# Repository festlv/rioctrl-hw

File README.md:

# rioctrl- a modular hardware for riocore

rioctrl is modular open source CNC controller hardware for [riocore](https://github.com/multigcs/riocore/).

It consists of a main FPGA controller board which has 6 slots for various input/output modules.

At this time, the following modules have been designed:

* [rioctrl-controller](rioctrl-controller/README.md): Lattice ECP5 based controller board
* [rioctrl-stepdir4](rioctrl-stepdir4/README.md): 4 axis step/dir output interface
* [rioctrl-quadenc4](rioctrl-quadenc4/README.md): 4 axis quadrature encoder (ABZ) input
* [rioctrl-shifio](rioctrl-shiftio/README.md): 16 digital inputs, 16 digital outputs (PNP)
* breakouts/lichuan-lc10: breakout board that allows connecting Lichuan LC10 series servo to stepdir4 and quadenc4 module (via off-the-shelf RJ45 cables)
* breakouts/rj45-screw-terminals: breakout board from RJ45 cable to screw terminals
* breakouts/ditron-dc11-encoder: breakout board from RJ45 cable to Ditron DC11 glass scale optical encoder (DB9)

# Current state of the hardware design

The following hardware has been built and tested to be working:

* rioctrl-controller v1.0: minor rework was needed (remove a diode, rotate Y1 by 90 degrees). Fixed in v1.1.
* rioctrl-stepdir4 v1.0: electrically working, mechanically a connector was offset by 4 mm, fixed in v1.1.
* rioctrl-shiftio: working as designed.
* rioctrl-quadencz: working as designed (with the caveat that it's only compatible with differential/RS422 encoders).
* breakouts/ditron-dc11-encoder: working as designed, tested with Ditron DC11 encoder with RS422 output option.
* breakouts/rj45-screw-terminals: working as designed.
* breakouts/lichuan-lc10: step/dir/enable working as designed, GPIOs not tested yet.

## Known issues

* External override for slot enable is slow to turn off stepdir enable signals. Need to scope this a bit, but it's either due to U14 output being
  tri-stated or the capacitance of +24V_EN lines powering the enable signals for some additional time.
# Pretty images

### rioctrl-controller

### rioctrl-stepdir4

### rioctrl-quadenc4

### rioctrl-shiftio

### breakouts/lichuan-lc10

### breakouts/rj45-screw-terminals

## build.py

There is a `build.py` script that publishes outputs to each module `outputs` directory. It uses `<module>/version` file to
determine the current version, which should be updated accordingly.

For 3D renders of the boards, kicad-nightly package is needed, as the currently stable kicad version does not have board rendering functionality available from command line.

# License

The hardware designs in this repository are licensed under [CERN Open Hardware Licence Version 2 - Strongly Reciprocal](LICENSE.md).

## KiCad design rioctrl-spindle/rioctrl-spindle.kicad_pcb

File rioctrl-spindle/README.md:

# rioctrl-spindle

This module provides:
* 2 analog outputs (0..10V)
* RS-485 interface for Modbus
* RS-422 interface (for full-duplex serial communication, pending software support)
* Differential encoder interface

__Only analog outputs and Modbus has been tested!__

## Pinout

|       |          |
|-------|----------|
| AIN0  | GND      |
| AIN1  | SER_TX_A |
| MODBUS_A | SER_TX_B |
| MODBUS_B | SER_RX_A |
| x     | SER_RX_B |

# Changelog

## v1.0
Initial released version.

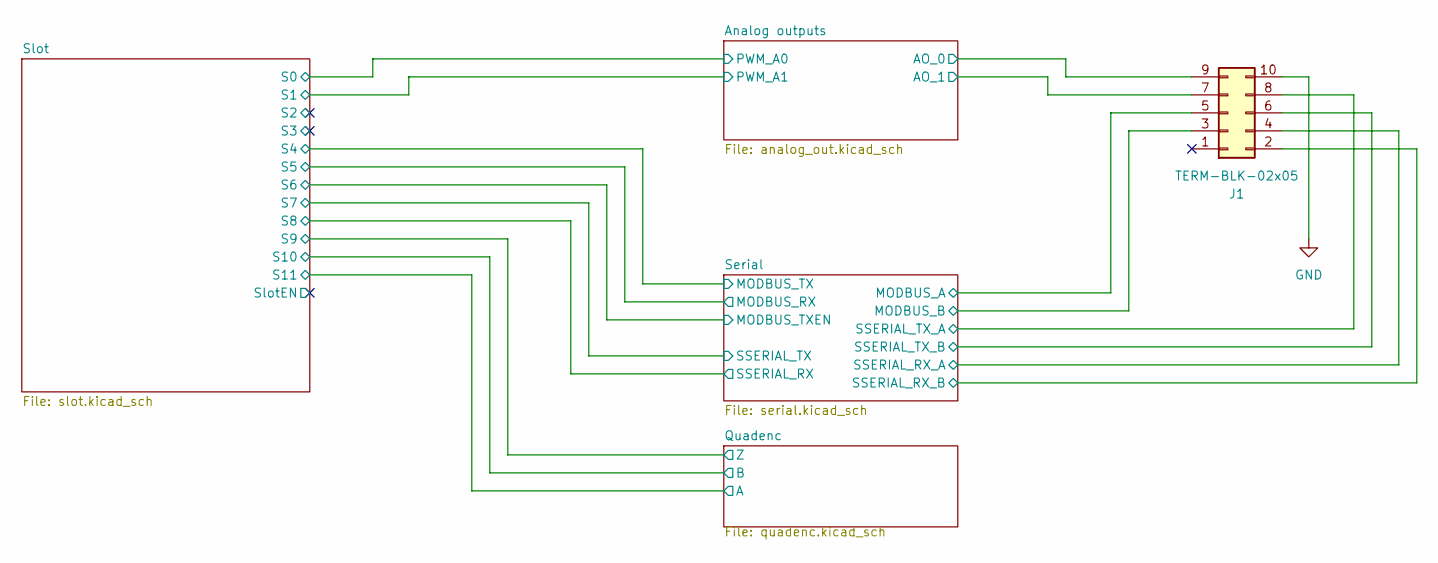
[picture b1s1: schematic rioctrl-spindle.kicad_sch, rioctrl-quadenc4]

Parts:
J1: TERM-BLK-02x05; JL15EDGRHC-35005B02; MPN JL15EDGRHC-35005B02; LCSC# C2908411

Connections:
/Analog outputs/AO_0: J1.9; also elsewhere on the board
/Analog outputs/AO_1: J1.7; also elsewhere on the board
/Serial/MODBUS_A: J1.5; also elsewhere on the board
/Serial/MODBUS_B: J1.3; also elsewhere on the board
/Serial/SSERIAL_RX_A: J1.4; also elsewhere on the board
/Serial/SSERIAL_RX_B: J1.2; also elsewhere on the board
/Serial/SSERIAL_TX_A: J1.8; also elsewhere on the board
/Serial/SSERIAL_TX_B: J1.6; also elsewhere on the board
GND: J1.10; also elsewhere on the board

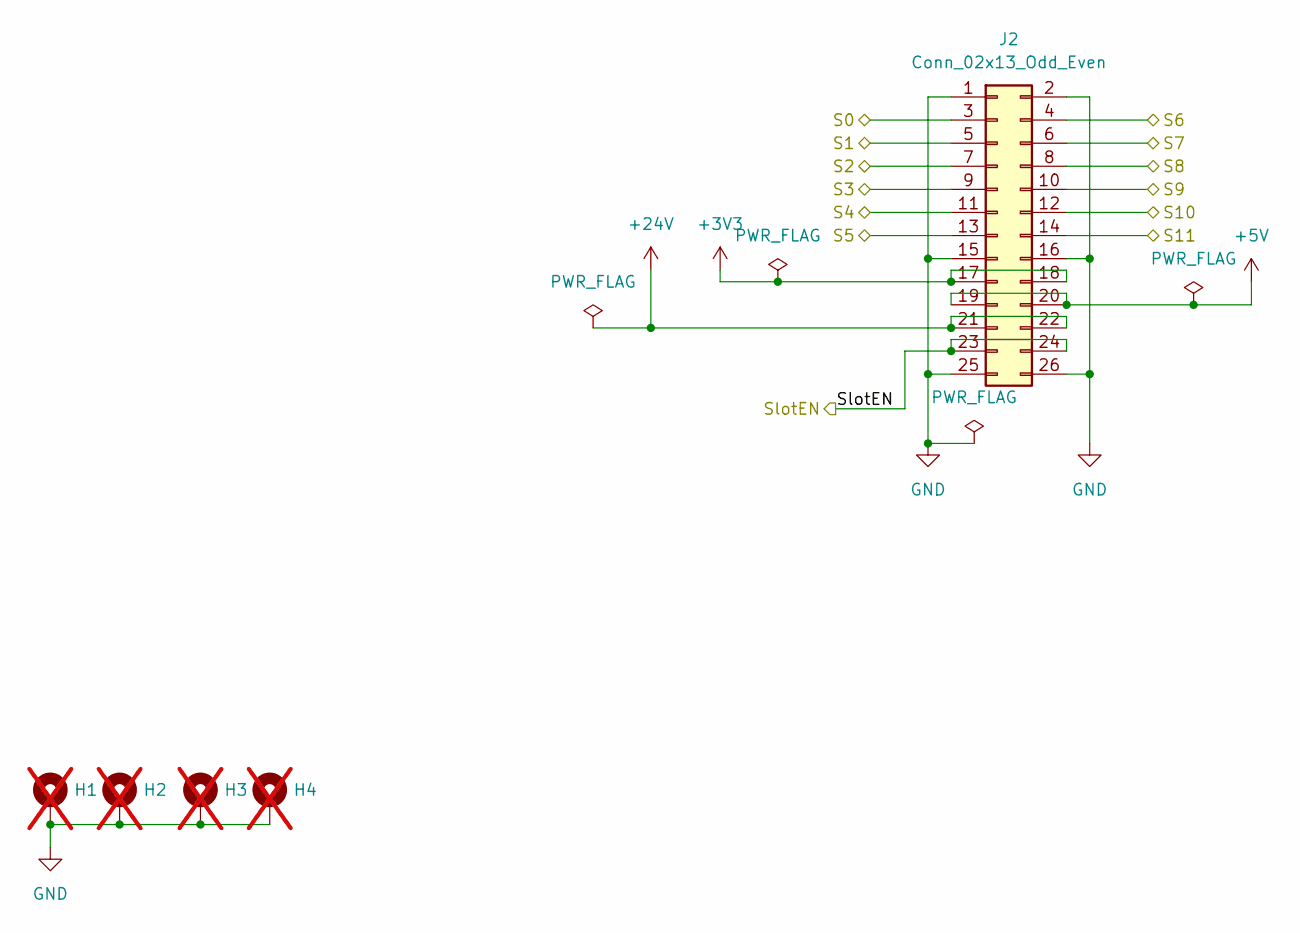
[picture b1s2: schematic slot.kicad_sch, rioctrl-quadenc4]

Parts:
H1, H2, H3, H4: MH_3.2mm; MountingHole_3.2mm_M3_Pad_Via; not fitted
J2: Conn_02x13_Odd_Even; PinHeader_2x13_P2.54mm_Horizontal; LCSC# C2894993

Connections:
+3V3: J2.17, J2.18; also elsewhere on the board
+5V: J2.19, J2.20; also elsewhere on the board
+24V: J2.21, J2.22; also elsewhere on the board
/Analog outputs/PWM_A0: J2.3; also elsewhere on the board
/Analog outputs/PWM_A1: J2.5; also elsewhere on the board
/Quadenc/A: J2.14; also elsewhere on the board
/Quadenc/B: J2.12; also elsewhere on the board
/Quadenc/Z: J2.10; also elsewhere on the board
/Serial/MODBUS_RX: J2.13; also elsewhere on the board
/Serial/MODBUS_TX: J2.11; also elsewhere on the board
/Serial/MODBUS_TXEN: J2.4; also elsewhere on the board
/Serial/SSERIAL_RX: J2.8; also elsewhere on the board
/Serial/SSERIAL_TX: J2.6; also elsewhere on the board
/Slot/S2: J2.7
/Slot/S3: J2.9
/Slot/SlotEN: J2.23, J2.24
GND: H1.1, H2.1, H3.1, H4.1, J2.1, J2.2, J2.15, J2.16, J2.25, J2.26; also elsewhere on the board

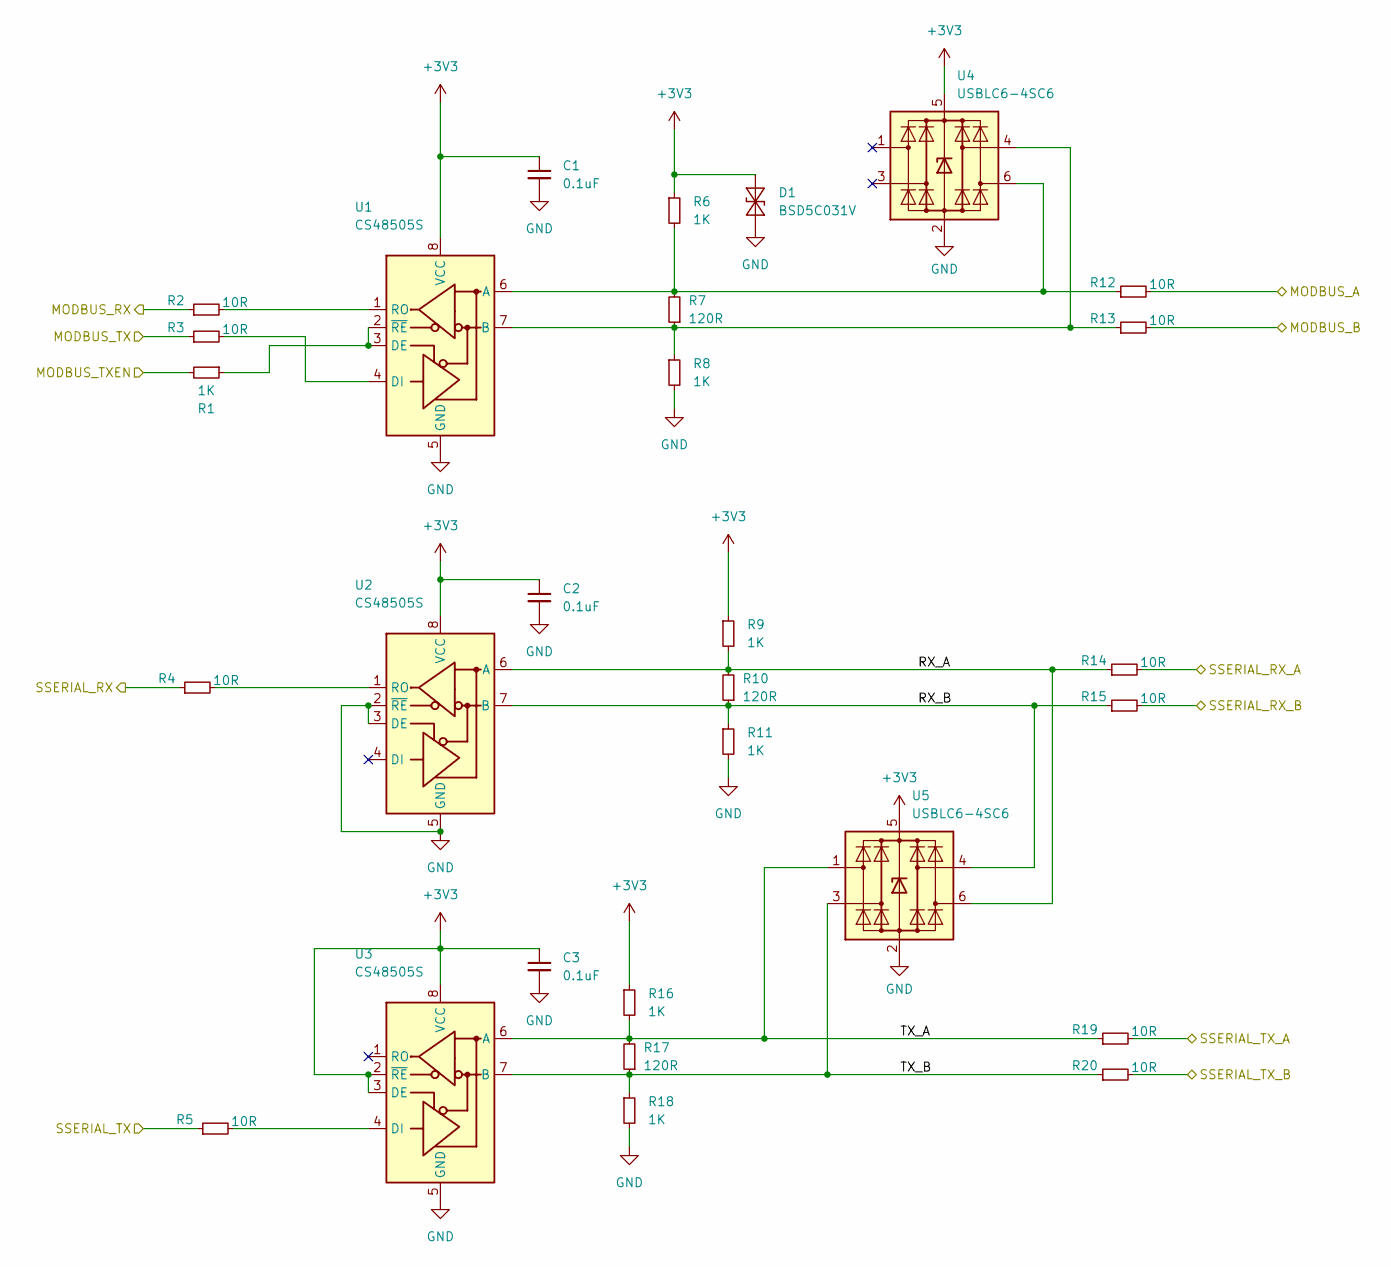
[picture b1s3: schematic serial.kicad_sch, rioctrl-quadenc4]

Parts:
C1, C2, C3: 0.1uF; C_0603_1608Metric; LCSC# C14663
D1: BSD5C031V; D_SOD-523; MPN BSD5C031V; LCSC# C151984
R1, R6, R8, R9, R11, R16, R18: 1K; R_0603_1608Metric; LCSC# C22548
R2, R3, R4, R5, R12, R13, R14, R15, R19, R20: 10R; R_0603_1608Metric; LCSC# C109318
R7, R10, R17: 120R; R_0603_1608Metric; LCSC# C114640
U1, U2, U3: CS48505S; SOIC-8_3.9x4.9mm_P1.27mm; MPN CS48505S; LCSC# C3202824
U4, U5: USBLC6-4SC6; SOT-23-6; MPN USBLC6-4SC6; LCSC# C5197386

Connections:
+3V3: C1.1, C2.1, C3.1, D1.1 (A1), R6.1, R9.1, R16.1, U1.8 (VCC), U2.8 (VCC), U3.2 (~RE), U3.3 (DE), U3.8 (VCC), U4.5 (VBUS), U5.5 (VBUS); also elsewhere on the board
/Serial/MODBUS_A: R12.2; also elsewhere on the board
/Serial/MODBUS_B: R13.2; also elsewhere on the board
/Serial/MODBUS_RX: R2.1; also elsewhere on the board
/Serial/MODBUS_TX: R3.1; also elsewhere on the board
/Serial/MODBUS_TXEN: R1.2; also elsewhere on the board
/Serial/RX_A: R9.2, R10.2, R14.1, U2.6 (A), U5.6 (I/O4)
/Serial/RX_B: R10.1, R11.1, R15.1, U2.7 (B), U5.4 (I/O3)
/Serial/SSERIAL_RX: R4.1; also elsewhere on the board
/Serial/SSERIAL_RX_A: R14.2; also elsewhere on the board
/Serial/SSERIAL_RX_B: R15.2; also elsewhere on the board
/Serial/SSERIAL_TX: R5.1; also elsewhere on the board
/Serial/SSERIAL_TX_A: R19.2; also elsewhere on the board
/Serial/SSERIAL_TX_B: R20.2; also elsewhere on the board
/Serial/TX_A: R16.2, R17.2, R19.1, U3.6 (A), U5.1 (I/O1)
/Serial/TX_B: R17.1, R18.1, R20.1, U3.7 (B), U5.3 (I/O2)
GND: C1.2, C2.2, C3.2, D1.2 (A2), R8.2, R11.2, R18.2, U1.5 (GND), U2.2 (~RE), U2.3 (DE), U2.5 (GND), U3.5 (GND), U4.2 (GND), U5.2 (GND); also elsewhere on the board
unnamed: R6.2, R7.2, R12.1, U1.6 (A), U4.6 (I/O4)
unnamed: R7.1, R8.1, R13.1, U1.7 (B), U4.4 (I/O3)
unnamed: R1.1, U1.2 (~RE), U1.3 (DE)
unnamed: R3.2, U1.4 (DI)
unnamed: R2.2, U1.1 (RO)
unnamed: R4.2, U2.1 (RO)
unnamed: R5.2, U3.4 (DI)

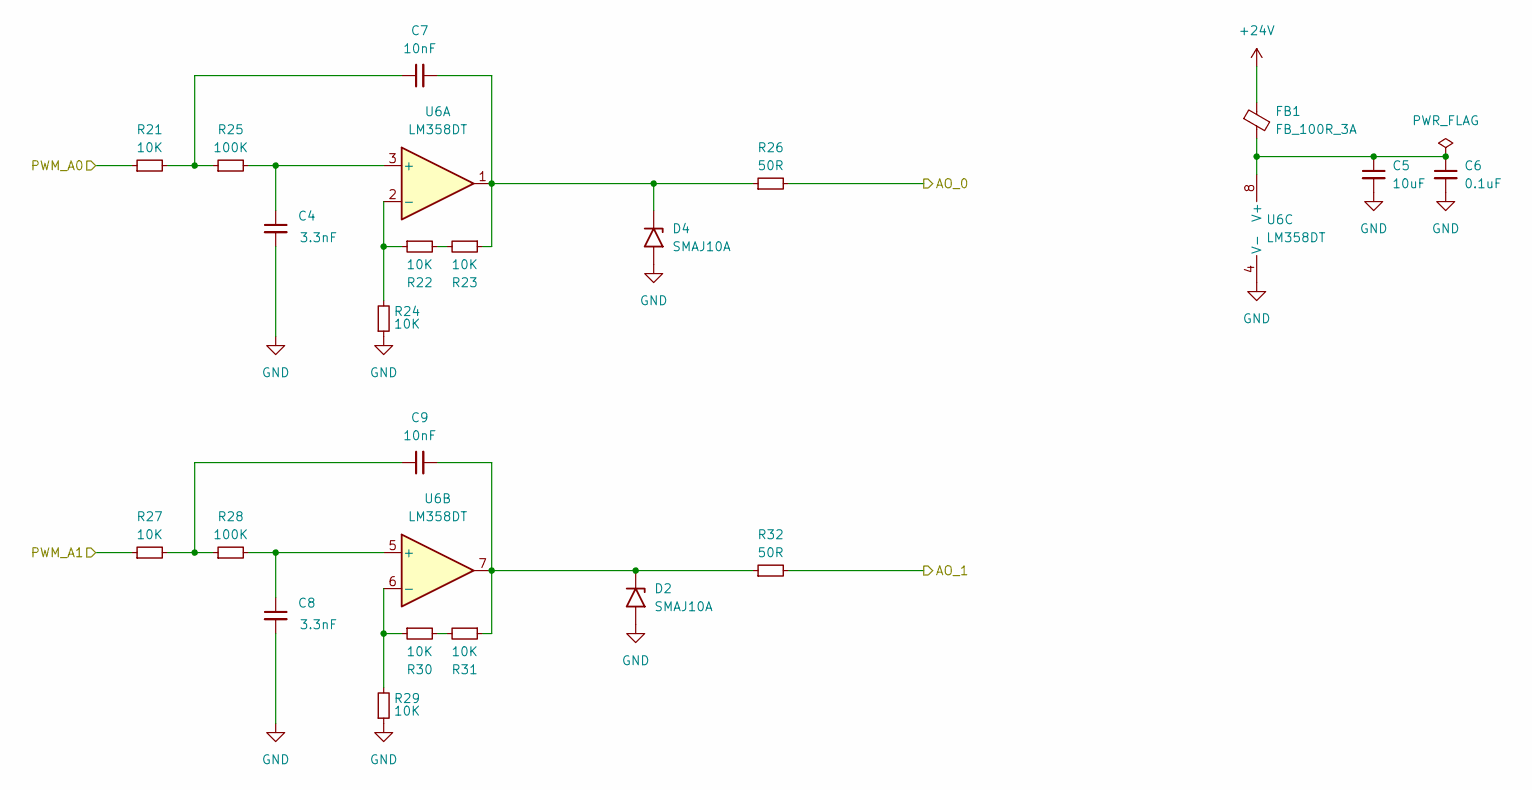
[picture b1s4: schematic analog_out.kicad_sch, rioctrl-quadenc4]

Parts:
C4, C8: 3.3nF; C_0603_1608Metric
C5: 10uF; C_0603_1608Metric
C6: 0.1uF; C_0603_1608Metric
C7, C9: 10nF; C_0603_1608Metric
D2, D4: SMAJ10A; D_SMA
FB1: FB_100R_3A; L_0603_1608Metric; MPN UPZ1608E101-3R0TF; LCSC# C96995
R21, R22, R23, R24, R27, R29, R30, R31: 10K; R_0603_1608Metric
R25, R28: 100K; R_0603_1608Metric
R26, R32: 50R; R_0603_1608Metric
U6: LM358DT; SO-8_3.9x4.9mm_P1.27mm; MPN LM358DT; LCSC# C9418

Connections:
+24V: FB1.1; also elsewhere on the board
/Analog outputs/AO_0: R26.2; also elsewhere on the board
/Analog outputs/AO_1: R32.2; also elsewhere on the board
/Analog outputs/PWM_A0: R21.1; also elsewhere on the board
/Analog outputs/PWM_A1: R27.1; also elsewhere on the board
GND: C4.2, C5.2, C6.2, C8.2, D2.2 (A2), D4.2 (A2), R24.1, R29.1, U6.4 (V-); also elsewhere on the board
unnamed: C7.1, R21.2, R25.1
unnamed: C9.1, R27.2, R28.1
unnamed: C9.2, D2.1 (A1), R31.1, R32.1, U6.7
unnamed: C7.2, D4.1 (A1), R23.1, R26.1, U6.1
unnamed: R22.2, R23.2
unnamed: R30.2, R31.2
unnamed: C4.1, R25.2, U6.3 (+)
unnamed: R22.1, R24.2, U6.2 (-)
unnamed: C8.1, R28.2, U6.5 (+)
unnamed: R29.2, R30.1, U6.6 (-)
unnamed: C5.1, C6.1, FB1.2, U6.8 (V+)

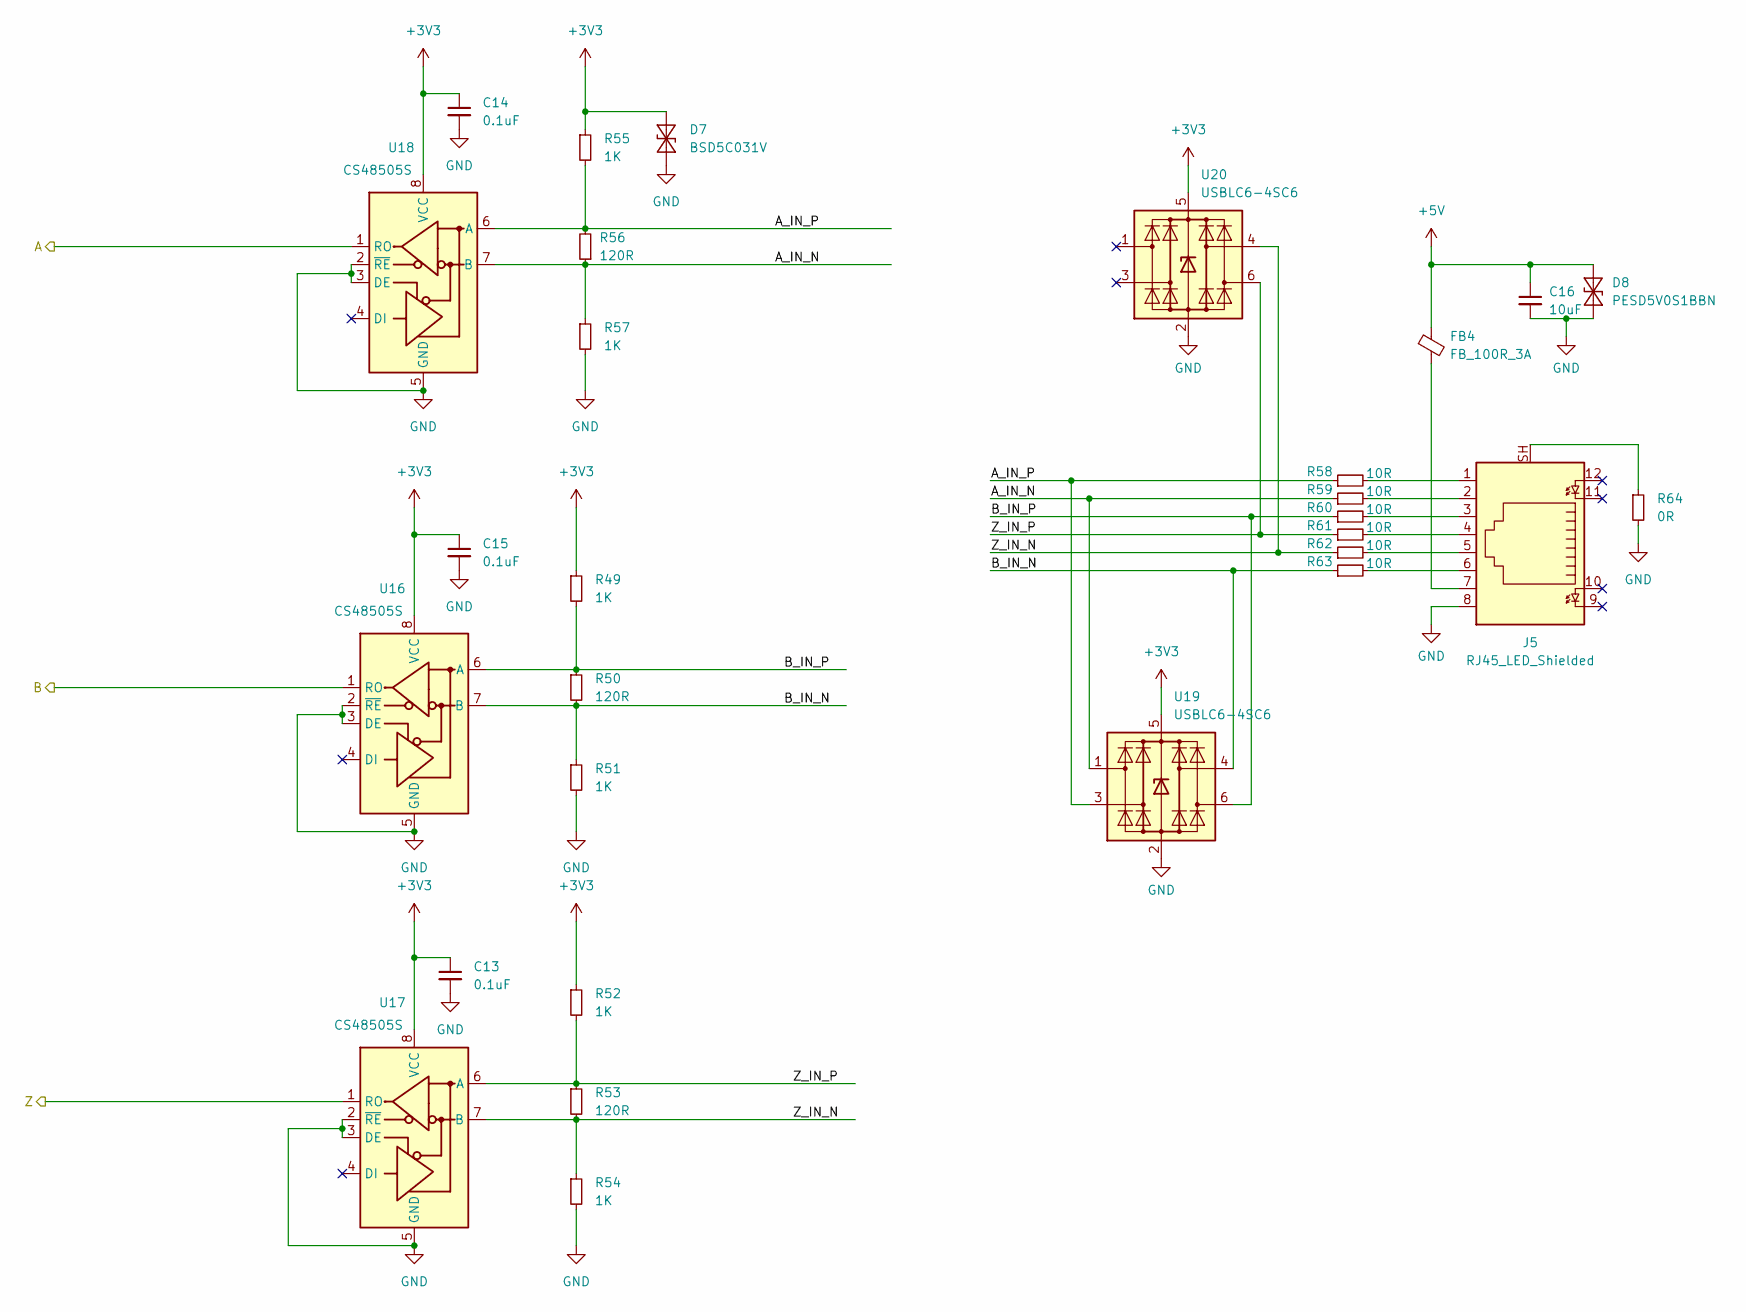
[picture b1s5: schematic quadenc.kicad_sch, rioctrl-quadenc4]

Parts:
C13, C14, C15: 0.1uF; C_0603_1608Metric; LCSC# C14663
C16: 10uF; C_0805_2012Metric; MPN GRM21BR61H106KE43L; LCSC# C440198
D7: BSD5C031V; D_SOD-523; MPN BSD5C031V; LCSC# C151984
D8: PESD5V0S1BBN; D_SOD-523; MPN PESD5V0S1BBN; LCSC# C314264
FB4: FB_100R_3A; L_0603_1608Metric; MPN UPZ1608E101-3R0TF; LCSC# C96995
J5: RJ45_LED_Shielded; R-RJ45R08P-C000; MPN R-RJ45R08P-C000; LCSC# C386757
R49, R51, R52, R54, R55, R57: 1K; R_0603_1608Metric; LCSC# C22548
R50, R53, R56: 120R; R_0603_1608Metric; LCSC# C114640
R58, R59, R60, R61, R62, R63: 10R; R_0603_1608Metric; LCSC# C109318
R64: 0R; R_0603_1608Metric; LCSC# C95177
U16, U17, U18: CS48505S; SOIC-8_3.9x4.9mm_P1.27mm; MPN CS48505S; LCSC# C3202824
U19, U20: USBLC6-4SC6; SOT-23-6; MPN USBLC6-4SC6; LCSC# C5197386

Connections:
+3V3: C13.1, C14.1, C15.1, D7.1 (A1), R49.1, R52.1, R55.1, U16.8 (VCC), U17.8 (VCC), U18.8 (VCC), U19.5 (VBUS), U20.5 (VBUS); also elsewhere on the board
+5V: C16.1, D8.2 (A2), FB4.1; also elsewhere on the board
/Quadenc/A: U18.1 (RO); also elsewhere on the board
/Quadenc/A_IN_N: R56.1, R57.1, R59.1, U18.7 (B), U19.1 (I/O1)
/Quadenc/A_IN_P: R55.2, R56.2, R58.1, U18.6 (A), U19.3 (I/O2)
/Quadenc/B: U16.1 (RO); also elsewhere on the board
/Quadenc/B_IN_N: R50.2, R51.1, R63.1, U16.7 (B), U19.4 (I/O3)
/Quadenc/B_IN_P: R49.2, R50.1, R60.1, U16.6 (A), U19.6 (I/O4)
/Quadenc/Z: U17.1 (RO); also elsewhere on the board
/Quadenc/Z_IN_N: R53.2, R54.1, R62.1, U17.7 (B), U20.4 (I/O3)
/Quadenc/Z_IN_P: R52.2, R53.1, R61.1, U17.6 (A), U20.6 (I/O4)
GND: C13.2, C14.2, C15.2, C16.2, D7.2 (A2), D8.1 (A1), J5.8, R51.2, R54.2, R57.2, R64.2, U16.2 (~RE), U16.3 (DE), U16.5 (GND), U17.2 (~RE), U17.3 (DE), U17.5 (GND), U18.2 (~RE), U18.3 (DE), U18.5 (GND), U19.2 (GND), U20.2 (GND); also elsewhere on the board
unnamed: FB4.2, J5.7
unnamed: J5.1, R58.2
unnamed: J5.2, R59.2
unnamed: J5.3, R60.2
unnamed: J5.4, R61.2
unnamed: J5.5, R62.2
unnamed: J5.6, R63.2
unnamed: J5.SH, R64.1

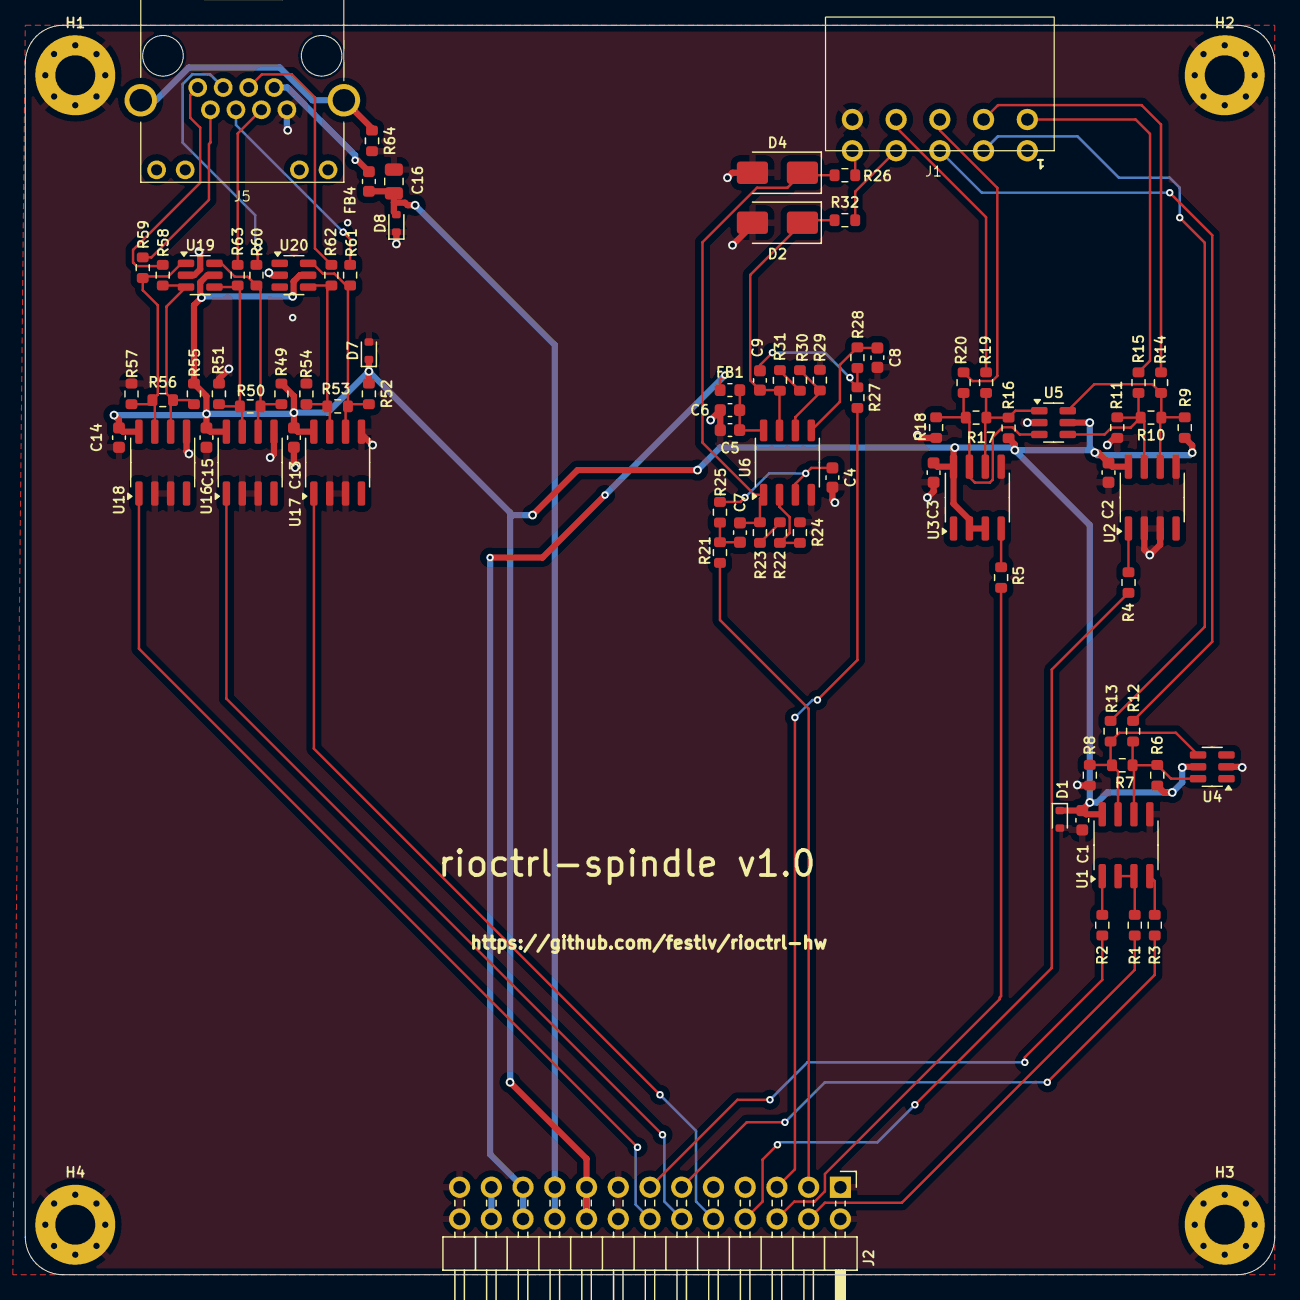
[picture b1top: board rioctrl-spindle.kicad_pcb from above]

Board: 2 copper layers, 100.0 x 100.0 mm, 86 parts (0 on the bottom side), 59 nets.

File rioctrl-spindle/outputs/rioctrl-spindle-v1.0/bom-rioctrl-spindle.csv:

"Refs","Value","Footprint","Manufacturer","MPN","Qty","DNP","LCSC#"
"C1-C3,C6,C13-C15","0.1uF","Capacitor_SMD:C_0603_1608Metric","","","7","","-- mixed values --"
"C4,C8","3.3nF","Capacitor_SMD:C_0603_1608Metric","","","2","",""
"C5","10uF","Capacitor_SMD:C_0603_1608Metric","","","1","",""
"C7,C9","10nF","Capacitor_SMD:C_0603_1608Metric","","","2","",""
"C16","10uF","Capacitor_SMD:C_0805_2012Metric","","GRM21BR61H106KE43L","1","","C440198"
"D1,D7","BSD5C031V","Diode_SMD:D_SOD-523","BORN","BSD5C031V","2","","C151984"
"D2,D4","SMAJ10A","Diode_SMD:D_SMA","","","2","",""
"D8","PESD5V0S1BBN","Diode_SMD:D_SOD-523","BORN","PESD5V0S1BBN","1","","C314264"
"FB1,FB4","FB_100R_3A","Inductor_SMD:L_0603_1608Metric","Sunlord","UPZ1608E101-3R0TF","2","","C96995"
"J1","TERM-BLK-02x05","hadv-connectors:JL15EDGRHC-35005B02","JILN","JL15EDGRHC-35005B02","1","","C2908411"
"J2","Conn_02x13_Odd_Even","Connector_PinHeader_2.54mm:PinHeader_2x13_P2.54mm_Horizontal","","","1","","C2894993"
"J5","RJ45_LED_Shielded","hadv-connectors:R-RJ45R08P-C000","Ckmtw(Shenzhen Cankemeng)","R-RJ45R08P-C000","1","","C386757"
"R1,R6,R8,R9,R11,R16,R18,R49,R51,R52,R54,R55,R57","1K","Resistor_SMD:R_0603_1608Metric","","","13","","C22548"
"R2-R5,R12-R15,R19,R20,R58-R63","10R","Resistor_SMD:R_0603_1608Metric","","","16","","C109318"
"R7,R10,R17,R50,R53,R56","120R","Resistor_SMD:R_0603_1608Metric","","","6","","C114640"
"R21-R24,R27,R29-R31","10K","Resistor_SMD:R_0603_1608Metric","","","8","",""
"R25,R28","100K","Resistor_SMD:R_0603_1608Metric","","","2","",""
"R26,R32","50R","Resistor_SMD:R_0603_1608Metric","","","2","",""
"R64","0R","Resistor_SMD:R_0603_1608Metric","","","1","","C95177"
"U1-U3,U16-U18","CS48505S","Package_SO:SOIC-8_3.9x4.9mm_P1.27mm","Chipanalog","CS48505S","6","","C3202824"
"U4,U5,U19,U20","USBLC6-4SC6","Package_TO_SOT_SMD:SOT-23-6","TECH PUBLIC","USBLC6-4SC6","4","","C5197386"
"U6","LM358DT","Package_SO:SO-8_3.9x4.9mm_P1.27mm","STMicroelectronics","LM358DT","1","","C9418"

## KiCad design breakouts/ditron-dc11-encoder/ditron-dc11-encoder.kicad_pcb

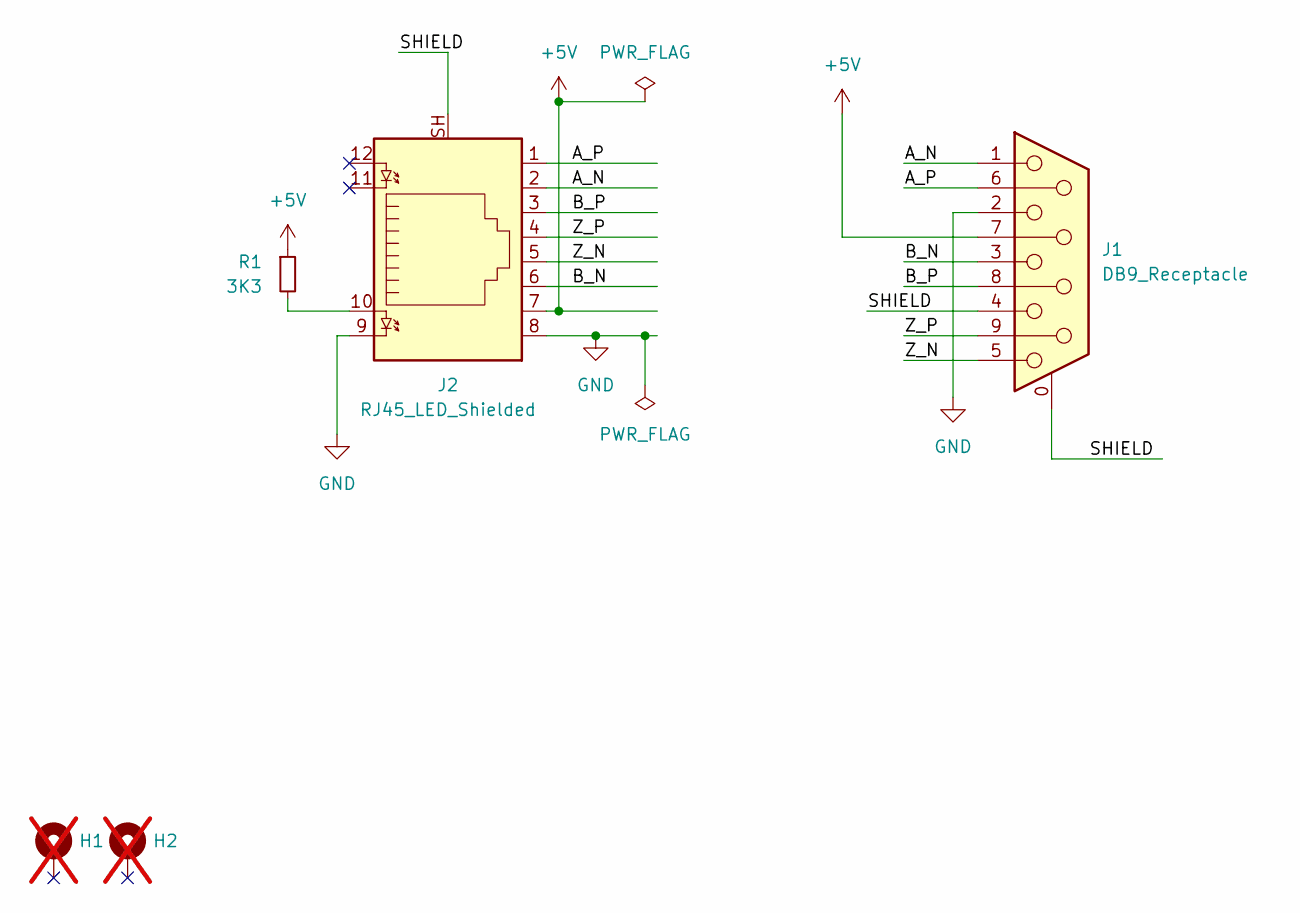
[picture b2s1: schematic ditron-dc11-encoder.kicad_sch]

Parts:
H1, H2: MH_3.2mm; MountingHole_3.2mm_M3_Pad_Via; not fitted
J1: DB9_Receptacle; DSUB-9_Female_Horizontal_P2.77x2.84mm_EdgePinOffset7.70mm_H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; MPN D-DMR009PF-D002; LCSC# C141882
J2: RJ45_LED_Shielded; R-RJ45R08P-C000; MPN R-RJ45R08P-C000; LCSC# C386757
R1: 3K3; R_0603_1608Metric; LCSC# C108078

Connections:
+5V: J1.7, J2.7, R1.1
/A_N: J1.1, J2.2
/A_P: J1.6, J2.1
/B_N: J1.3, J2.6
/B_P: J1.8, J2.3
/SHIELD: J1.0 (PAD), J1.4, J2.SH
/Z_N: J1.5, J2.5
/Z_P: J1.9, J2.4
GND: J1.2, J2.8, J2.9
unnamed: J2.10, R1.2

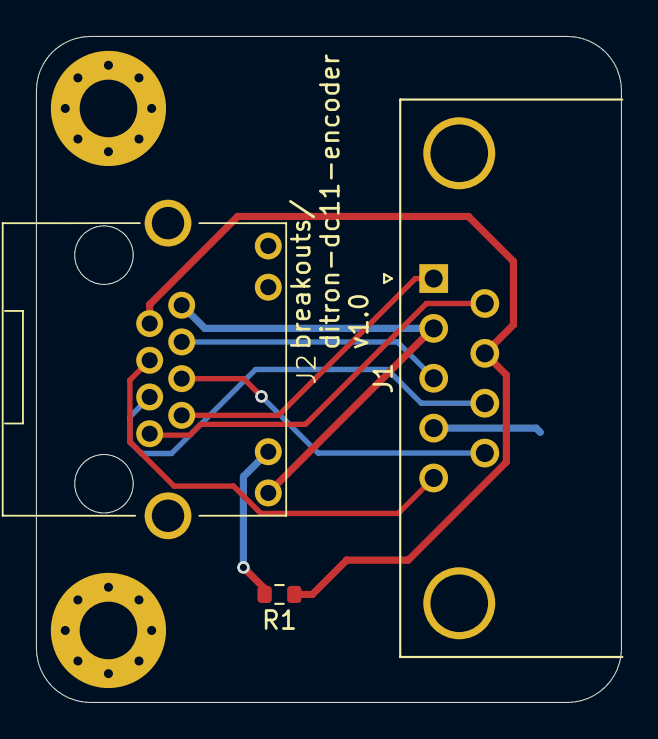
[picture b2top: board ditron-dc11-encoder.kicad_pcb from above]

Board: 2 copper layers, 32.5 x 37.0 mm, 5 parts (0 on the bottom side), 10 nets.

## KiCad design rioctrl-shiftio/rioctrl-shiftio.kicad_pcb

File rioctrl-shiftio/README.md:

# rioctrl-shiftio

This module provides the following IOs:
* 16 opto-isolated digital outputs (PNP, external voltage input 5-24V in two groups). Each output is capable of sourcing ~0.6A of current and has over-current protection.
* 16 opto-isolated digital inputs (12-24V, both sourcing and sinking connections are possible).

Due to slot width limitations, each group of outputs (4 in total) are fitted with spring-type pluggable terminal blocks (LCSC part number:
[C2908401](https://www.lcsc.com/product-detail/Pluggable-System-Terminal-Block_JILN-JL15EDGKNH-35005B01_C2908401.html)).

# Pinout

## Pinout of output blocks

VCC is 5..24V DC. Each of the output blocks has a separate power supply, so for example
one block can be 5V outputs and another one- 24VDC.

| VCC  | GND  |
|------|------|
| 0    | 1    |
| 2    | 3    |
| 4    | 5    |
| 6    | 7    |

| VCC | GND |
|-----|-----|
| 8   | 9   |
| 10  | 11  |
| 12  | 13  |
| 14  | 15  |

## Pinout of input blocks

Common input can be either ground, or positive voltage of 12..24VDC for sourcing or 
sinking type outputs.

Limited testing has shown that inputs also work at 5V output level, but that's not really guaranteed with the
values of components in current design.

|   | Common |
|---|---------|
| 0 | 1       |
| 2 | 3       |
| 4 | 5       |
| 6 | 7       |

|  | Common |
|-----|--------|
| 8   | 9      |
| 10  | 11     |
| 12  | 13     |
| 14  | 15     |

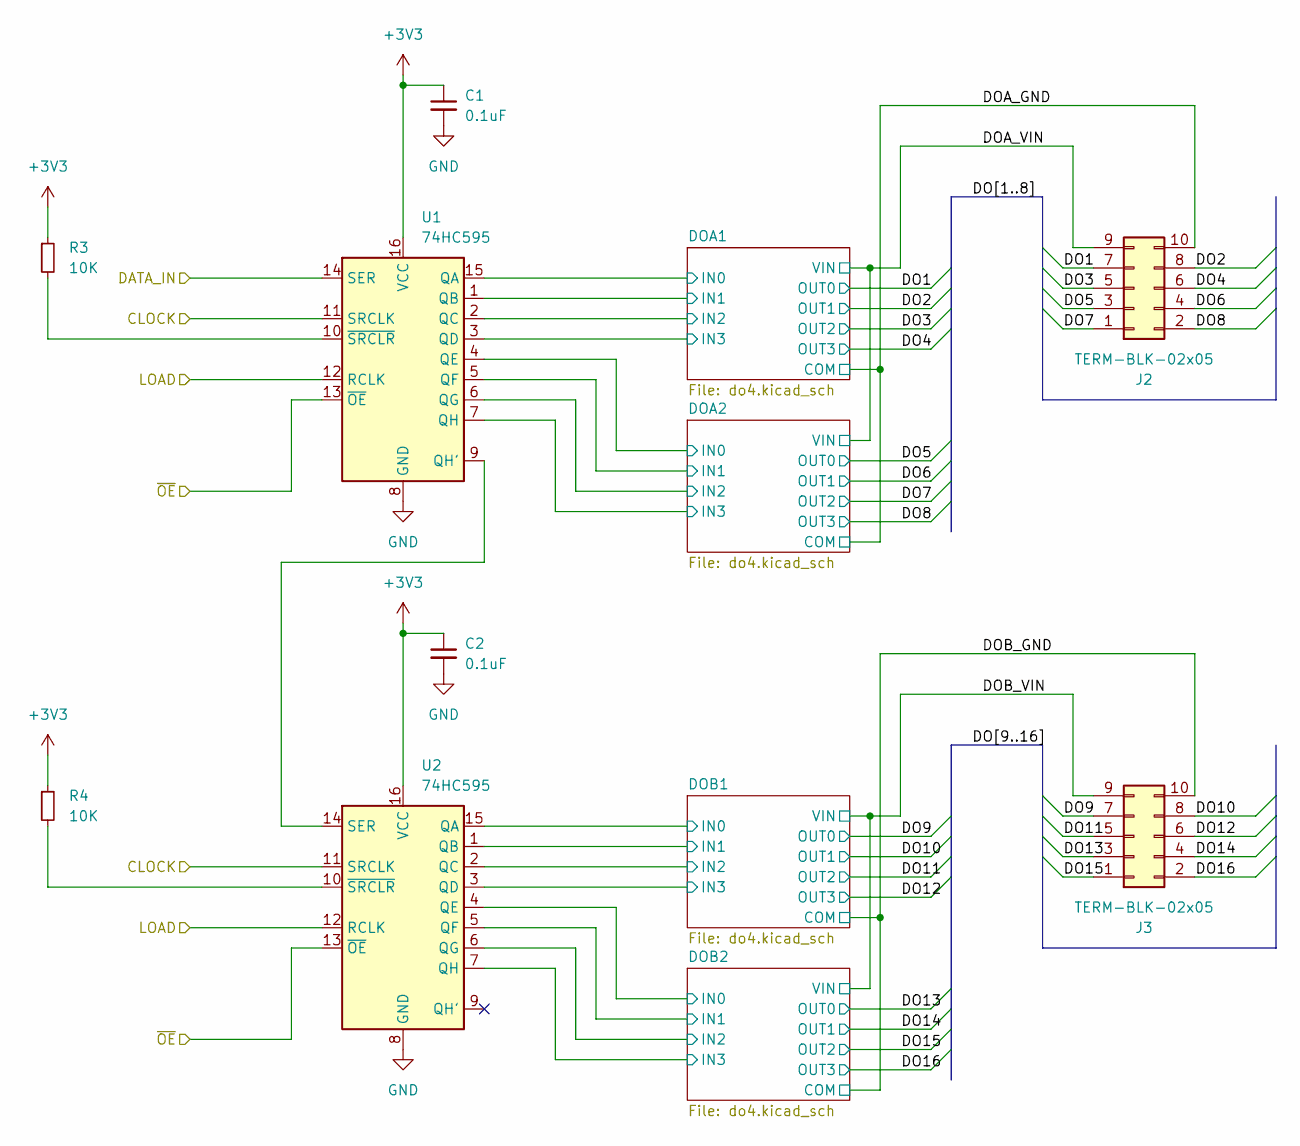
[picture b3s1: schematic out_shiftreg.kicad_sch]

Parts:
C1, C2: 0.1uF; C_0603_1608Metric; LCSC# C14663
J2, J3: TERM-BLK-02x05; JL15EDGRHC-35005B02; MPN JL15EDGRHC-35005B02; LCSC# C2908411
R3, R4: 10K; R_0603_1608Metric; LCSC# C98220
U1, U2: 74HC595; SO-16_3.9x9.9mm_P1.27mm; MPN 74HC595D,118; LCSC# C5947

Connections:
+3V3: C1.1, C2.1, R3.1, R4.1, U1.16 (VCC), U2.16 (VCC); also elsewhere on the board
/Output shiftreg/CLOCK: U1.11 (SRCLK), U2.11 (SRCLK); also elsewhere on the board
/Output shiftreg/DATA_IN: U1.14 (SER); also elsewhere on the board
/Output shiftreg/DO1: J2.7; also elsewhere on the board
/Output shiftreg/DO2: J2.8; also elsewhere on the board
/Output shiftreg/DO3: J2.5; also elsewhere on the board
/Output shiftreg/DO4: J2.6; also elsewhere on the board
/Output shiftreg/DO5: J2.3; also elsewhere on the board
/Output shiftreg/DO6: J2.4; also elsewhere on the board
/Output shiftreg/DO7: J2.1; also elsewhere on the board
/Output shiftreg/DO8: J2.2; also elsewhere on the board
/Output shiftreg/DO9: J3.7; also elsewhere on the board
/Output shiftreg/DO10: J3.8; also elsewhere on the board
/Output shiftreg/DO11: J3.5; also elsewhere on the board
/Output shiftreg/DO12: J3.6; also elsewhere on the board
/Output shiftreg/DO13: J3.3; also elsewhere on the board
/Output shiftreg/DO14: J3.4; also elsewhere on the board
/Output shiftreg/DO15: J3.1; also elsewhere on the board
/Output shiftreg/DO16: J3.2; also elsewhere on the board
/Output shiftreg/DOA1/IN0: U1.15 (QA); also elsewhere on the board
/Output shiftreg/DOA1/IN1: U1.1 (QB); also elsewhere on the board
/Output shiftreg/DOA1/IN2: U1.2 (QC); also elsewhere on the board
/Output shiftreg/DOA1/IN3: U1.3 (QD); also elsewhere on the board
/Output shiftreg/DOA2/IN0: U1.4 (QE); also elsewhere on the board
/Output shiftreg/DOA2/IN1: U1.5 (QF); also elsewhere on the board
/Output shiftreg/DOA2/IN2: U1.6 (QG); also elsewhere on the board
/Output shiftreg/DOA2/IN3: U1.7 (QH); also elsewhere on the board
/Output shiftreg/DOA_GND: J2.10; also elsewhere on the board
/Output shiftreg/DOA_VIN: J2.9; also elsewhere on the board
/Output shiftreg/DOB1/IN0: U2.15 (QA); also elsewhere on the board
/Output shiftreg/DOB1/IN1: U2.1 (QB); also elsewhere on the board
/Output shiftreg/DOB1/IN2: U2.2 (QC); also elsewhere on the board
/Output shiftreg/DOB1/IN3: U2.3 (QD); also elsewhere on the board
/Output shiftreg/DOB2/IN0: U2.4 (QE); also elsewhere on the board
/Output shiftreg/DOB2/IN1: U2.5 (QF); also elsewhere on the board
/Output shiftreg/DOB2/IN2: U2.6 (QG); also elsewhere on the board
/Output shiftreg/DOB2/IN3: U2.7 (QH); also elsewhere on the board
/Output shiftreg/DOB_GND: J3.10; also elsewhere on the board
/Output shiftreg/DOB_VIN: J3.9; also elsewhere on the board
/Output shiftreg/LOAD: U1.12 (RCLK), U2.12 (RCLK); also elsewhere on the board
/Output shiftreg/~OE: U1.13 (~OE), U2.13 (~OE); also elsewhere on the board
GND: C1.2, C2.2, U1.8 (GND), U2.8 (GND); also elsewhere on the board
unnamed: U1.9 (QH'), U2.14 (SER)
unnamed: R3.2, U1.10 (~SRCLR)
unnamed: R4.2, U2.10 (~SRCLR)

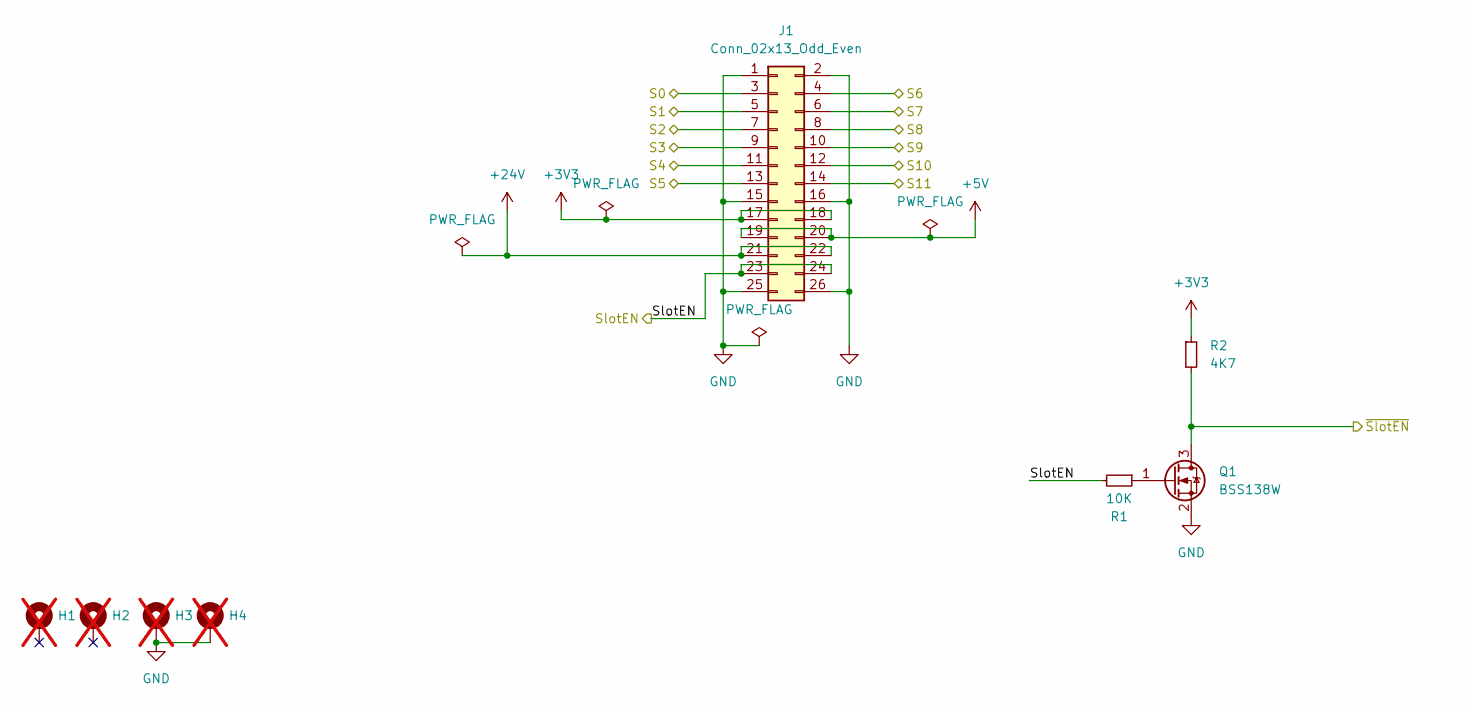
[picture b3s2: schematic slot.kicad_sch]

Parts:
H1, H2, H3, H4: MH_3.2mm; MountingHole_3.2mm_M3_Pad_Via; not fitted
J1: Conn_02x13_Odd_Even; PinHeader_2x13_P2.54mm_Horizontal; LCSC# C2894993
Q1: BSS138W; SOT-323_SC-70; MPN BSS138W; LCSC# C504052
R1: 10K; R_0603_1608Metric; LCSC# C98220
R2: 4K7; R_0603_1608Metric; LCSC# C99782

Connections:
+3V3: J1.17, J1.18, R2.1; also elsewhere on the board
+5V: J1.19, J1.20
+24V: J1.21, J1.22
/Input shiftreg/CLK: J1.11; also elsewhere on the board
/Input shiftreg/DATA_OUT: J1.9; also elsewhere on the board
/Input shiftreg/LOAD: J1.13; also elsewhere on the board
/Output shiftreg/CLOCK: J1.5; also elsewhere on the board
/Output shiftreg/DATA_IN: J1.3; also elsewhere on the board
/Output shiftreg/LOAD: J1.7; also elsewhere on the board
/Output shiftreg/~OE: Q1.3 (D), R2.2; also elsewhere on the board
/Slot/S6: J1.4
/Slot/S7: J1.6
/Slot/S8: J1.8
/Slot/S9: J1.10
/Slot/S10: J1.12
/Slot/S11: J1.14
/Slot/SlotEN: J1.23, J1.24, R1.2
GND: H3.1, H4.1, J1.1, J1.2, J1.15, J1.16, J1.25, J1.26, Q1.2 (S); also elsewhere on the board
unnamed: Q1.1 (G), R1.1
